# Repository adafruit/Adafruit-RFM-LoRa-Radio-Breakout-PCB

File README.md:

## Adafruit RFM LoRa Radio Breakout PCB
<a href="http://www.adafruit.com/products/3070"><br/>
Click here to purchase one from the Adafruit shop</a>

"You see, wire telegraph is a kind of a very, very long cat.  You pull his tail in New York and his head is meowing in Los Angeles.  Do you understand this? And radio operates exactly the same way: you send signals here, they receive them there.  The only difference is that there is no cat."

Sending data over long distances is like magic, and now you can be a magician with this range of powerful and easy-to-use radio modules. Sure, sometimes you want to talk to a computer (a good time to use WiFi) or perhaps communicate with a Phone (choose Bluetooth Low Energy!) but what if you want to send data very far? Most WiFi, Bluetooth, Zigbee and other wireless chipsets use 2.4GHz, which is great for high speed transfers. If you aren't so concerned about streaming a video, you can use a lower license-free frequency such as 433 or 900 MHz. You can't send data as fast but you can send data a lot farther.'

Also, these packet radios are simpler than WiFi or BLE, you dont have to associate, pair, scan, or worry about connections. All you do is send data whenever you like, and any other modules tuned to that same frequency (and, with the same encryption key) will receive. The receiver can then send a reply back. The modules do packetization, error correction and can also auto-retransmit so its not like you have worry about everything but less power is wasted on maintaining a link or pairing.

These modules are great for use with Arduinos or other microcontrollers, say if you want a sensor node nework or transmit data over a campus or town. The trade off is you need two or more radios, with matching frequencies. WiFi and BT, on the other hand, are commonly included in computers and phones.

These radio modules come in four variants (two modulation types and two frequencies) The RFM69's are easiest to work with, and are well known and understood. The LoRa radios are exciting and more powerful but also more expensive.

First there is the 900 MHz radio version, which can be used for either 868MHz or 915MHz transmission/reception - the exact radio frequency is determined when you load the software since it can be tuned around dynamically. We also carry an RFM69HCW 433 MHz version here. These are +20dBm FSK packet radios that have a lot of nice extras in them such as encryption and auto-retransmit. They can go at least 500 meters line of sight using simple wire antennas, probably up to 5Km with directional antennas and settings tweakings

For more details, check out the product pages for various models at

   * http://www.adafruit.com/product/3070
   * http://www.adafruit.com/product/3071
   * http://www.adafruit.com/product/3072
   * http://www.adafruit.com/product/3073
   
PCB files for the Adafruit RFM/LoRa Radio Breakouts. The format is EagleCAD schematic and board layout

### License

Adafruit invests time and resources providing this open source design, please support Adafruit and open-source hardware by purchasing products from [Adafruit](https://www.adafruit.com)!

All text above must be included in any redistribution

Designed by Limor Fried/Ladyada for Adafruit Industries.
Creative Commons Attribution/Share-Alike, all text above must be included in any redistribution. 
See license.txt for additional information.

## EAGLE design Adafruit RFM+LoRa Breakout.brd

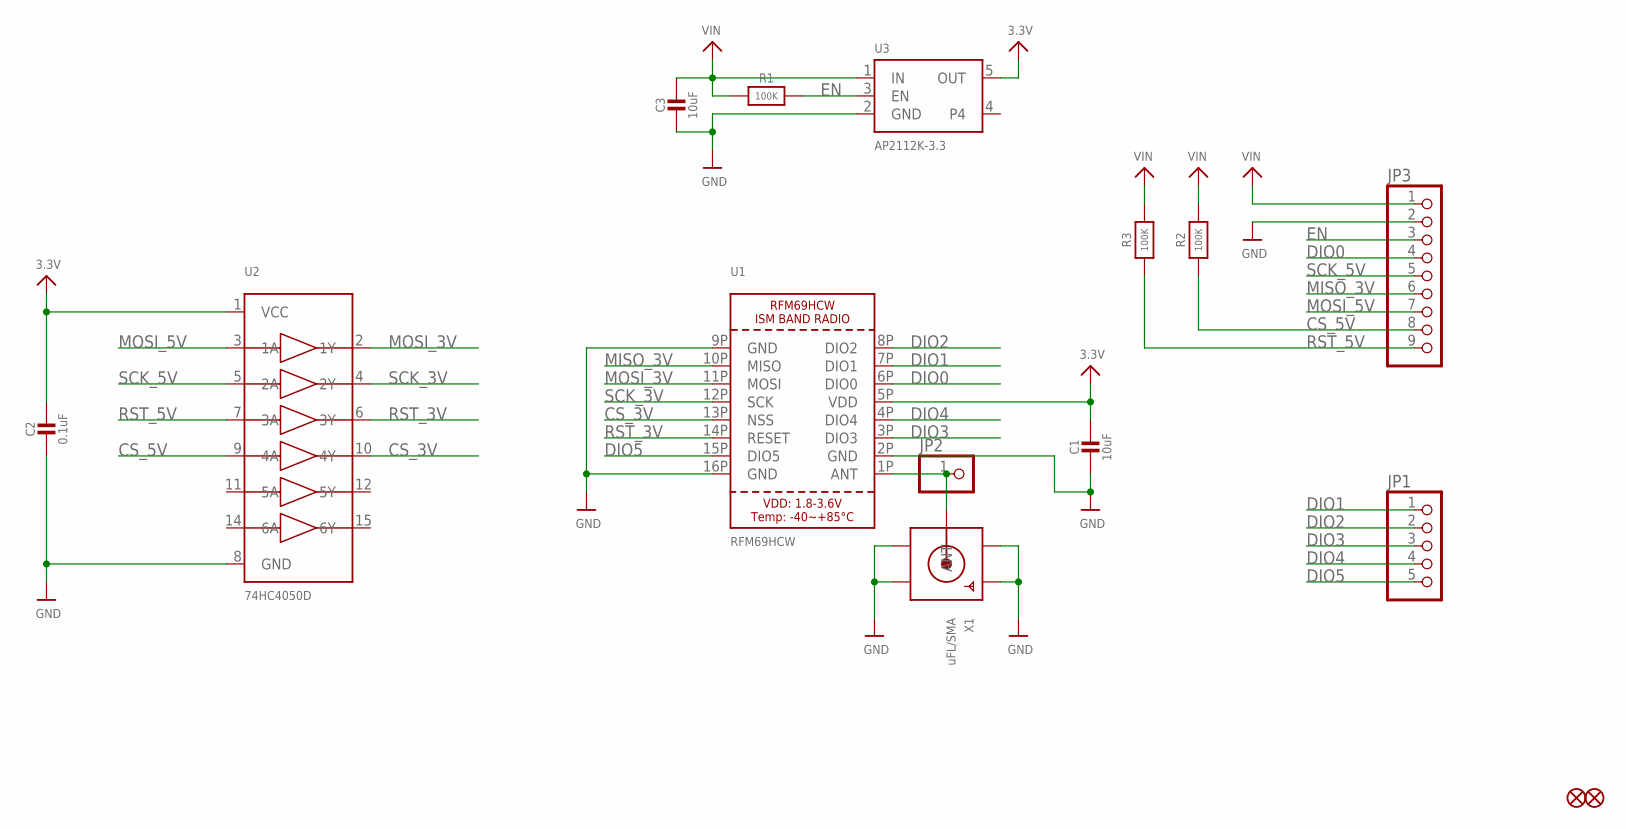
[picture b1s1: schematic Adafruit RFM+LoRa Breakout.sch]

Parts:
C1, C3: 10uF; 0805-NO
C2: 0.1uF; 0805-NO
FID1, FID2: FIDUCIAL""; FIDUCIAL_1MM
JP1: HEADER-1X570MIL; 1X05_ROUND_70
JP2: HEADER-1X1ROUND; 1X01_ROUND
JP3: HEADER-1X970MIL; 1X09_ROUND_70
R1, R2, R3: 100K; 0805-NO
U1: RFM69HCW; RFMHCW_SMT
U2: 74HC4050D; TSSOP16
U3: AP2112K-3.3; SOT23-5
X1: uFL/SMA; SMA_EDGELAUNCH_UFL

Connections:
3.3V: C1.1, C2.1, U1.5P (VDD), U2.1 (VCC), U3.5 (OUT)
CS_3V: U1.13P (NSS), U2.10 (4Y)
CS_5V: JP3.8, R2.1, U2.9 (4A)
DIO0: JP3.4, U1.6P (DIO0)
DIO1: JP1.1, U1.7P (DIO1)
DIO2: JP1.2, U1.8P (DIO2)
DIO3: JP1.3, U1.3P (DIO3)
DIO4: JP1.4, U1.4P (DIO4)
DIO5: JP1.5, U1.15P (DIO5)
EN: JP3.3, R1.2, U3.3 (EN)
GND: C1.2, C2.2, C3.2, JP3.2, U1.2P (GND), U1.9P (GND), U1.16P (GND), U2.8 (GND), U3.2 (GND), X1.GND@1 (GND1), X1.GND@2 (GND2), X1.GND@3 (GND3), X1.GND@4 (GND4)
MISO_3V: JP3.6, U1.10P (MISO)
MOSI_3V: U1.11P (MOSI), U2.2 (1Y)
MOSI_5V: JP3.7, U2.3 (1A)
unnamed: JP2.1, U1.1P (ANT), X1.P (ANT)
RST_3V: U1.14P (RESET), U2.6 (3Y)
RST_5V: JP3.9, R3.1, U2.7 (3A)
SCK_3V: U1.12P (SCK), U2.4 (2Y)
SCK_5V: JP3.5, U2.5 (2A)
VIN: C3.1, JP3.1, R1.1, R2.2, R3.2, U3.1 (IN)

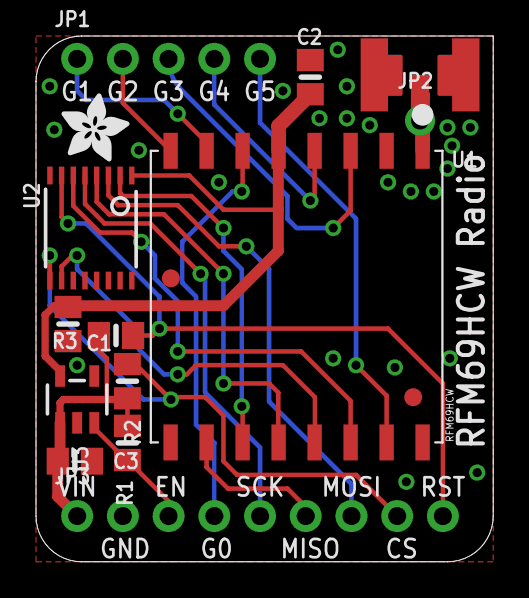
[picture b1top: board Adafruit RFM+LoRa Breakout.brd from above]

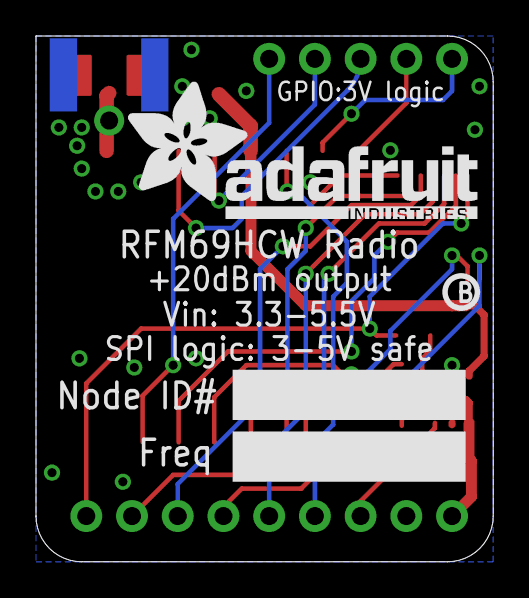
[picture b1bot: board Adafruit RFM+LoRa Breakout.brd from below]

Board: 2 copper layers, 25.4 x 29.2 mm, 18 parts (2 on the bottom side), 20 nets.

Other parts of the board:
U$8: ADAFRUIT_3.5MM
U$14: PCBFEAT-REV-040
U$19: ADAFRUIT_TEXT_20MM

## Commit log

2016-06-14 init!

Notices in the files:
parts and their libraries:
microbuilder: This work is placed in the public domain, and may be freely used for commercial and non-commercial work with the following conditions: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
